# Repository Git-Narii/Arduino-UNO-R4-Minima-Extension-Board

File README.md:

# Arduino-UNO-R4-Minima-Extension-Board

Arduino UNO R4 Minima用拡張基板

PCBファイルは未編集

kiCAD操作練習用

各自が使いやすいよう配線、配置してください

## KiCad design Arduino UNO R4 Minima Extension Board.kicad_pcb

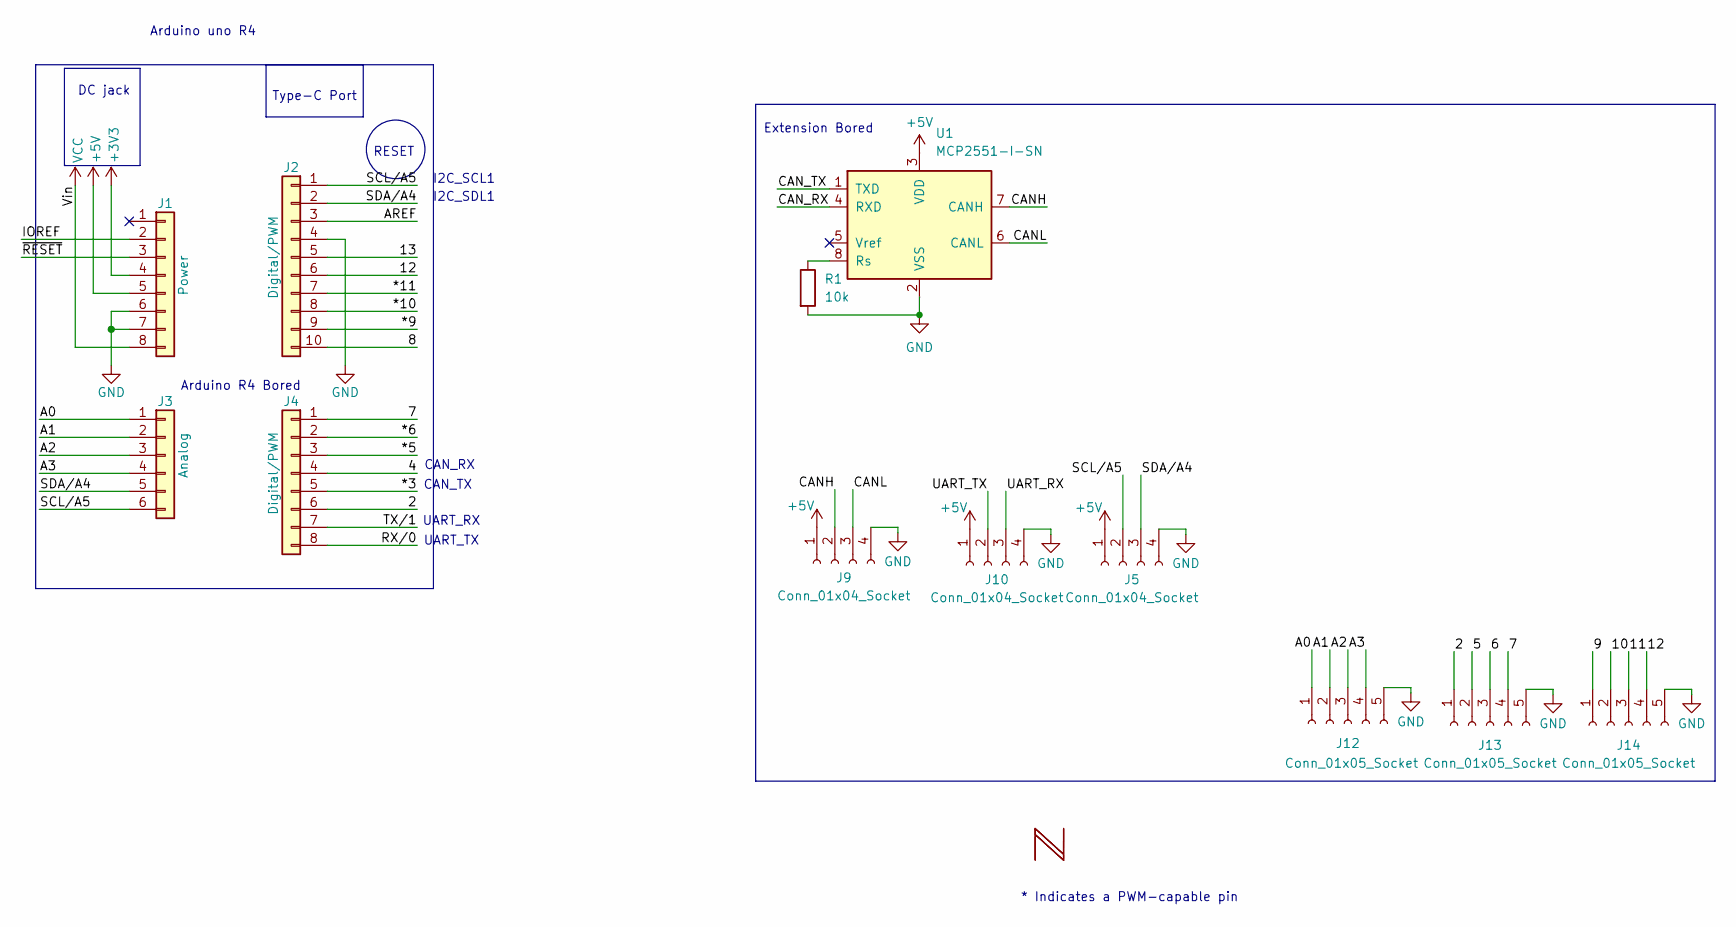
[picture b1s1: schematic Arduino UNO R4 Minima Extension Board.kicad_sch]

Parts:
J1: Power; PinSocket_1x08_P2.54mm_Vertical
J2: Digital/PWM; PinSocket_1x10_P2.54mm_Vertical
J3: Analog; PinSocket_1x06_P2.54mm_Vertical
J4: Digital/PWM; PinSocket_1x08_P2.54mm_Vertical
J5, J9, J10: Conn_01x04_Socket; JST_XA_S04B-XASK-1_1x04_P2.50mm_Horizontal
J12, J13, J14: Conn_01x05_Socket; JST_XA_S05B-XASK-1_1x05_P2.50mm_Horizontal
R1: 10k; R_0603_1608Metric
U1: MCP2551-I-SN; SOIC-8_3.9x4.9mm_P1.27mm

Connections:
+3V3: J1.4
+5V: J1.5, J5.1, J9.1, J10.1, U1.3 (VDD)
/2: J4.6, J13.1
/4: J4.4
/5: J13.2
/6: J13.3
/7: J4.1, J13.4
/8: J2.10
/9: J14.1
/10: J14.2
/11: J14.3
/12: J2.6, J14.4
/13: J2.5
/*3: J4.5
/*5: J4.3
/*6: J4.2
/*9: J2.9
/*10: J2.8
/*11: J2.7
/A0: J3.1, J12.1
/A1: J3.2, J12.2
/A2: J3.3, J12.3
/A3: J3.4, J12.4
/AREF: J2.3
/CANH: J9.2, U1.7 (CANH)
/CANL: J9.3, U1.6 (CANL)
/CAN_RX: U1.4 (RXD)
/CAN_TX: U1.1 (TXD)
/IOREF: J1.2
/RX/0: J4.8
/SCL/A5: J2.1, J3.6, J5.2
/SDA/A4: J2.2, J3.5, J5.3
/TX/1: J4.7
/UART_RX: J10.3
/UART_TX: J10.2
/~RESET: J1.3
GND: J1.6, J1.7, J2.4, J5.4, J9.4, J10.4, J12.5, J13.5, J14.5, R1.2, U1.2 (VSS)
unnamed: R1.1, U1.8 (Rs)
VCC: J1.8

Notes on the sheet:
DC jack
UART_RX
Arduino R4 Bored
UART_TX
Arduino uno R4
Extension Bored
I2C_SDL1
* Indicates a PWM-capable pin
RESET
CAN_RX
CAN_TX
I2C_SCL1
Type-C Port

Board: 2 copper layers, 17 parts (0 on the bottom side), 14 nets, no tracks yet.

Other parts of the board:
J11: Conn_01x05_Socket; JST_XA_S05B-XASK-1_1x05_P2.50mm_Horizontal
MH1, MH2, MH3, MH4: MountingHole_3.2mm
